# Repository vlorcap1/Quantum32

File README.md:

# Sistema de Análisis de Opiniones Distribuido I2C

## Changelog / Recent Updates (Quantum32 V3)
- **2025-12-22**:
  - **Fixed Blocking**: Master V3 now updates the OLED display continuously, even during high-speed Python batched sampling.
  - **Fixed Slave LED**: Slaves now explicitly use **Pin 7** for the status LED and give visual feedback on every I2C RX/TX event.
  - **Environment**: Fixed local Python environment initialization.

Sistema distribuido basado en Arduino que utiliza comunicación I2C para coordinar múltiples dispositivos esclavos que realizan análisis de opiniones (a favor/en contra/neutral). El maestro agrega los resultados y los muestra en una pantalla OLED con marcas de tiempo del RTC.

## 📋 Descripción

Este proyecto implementa una **simulación pedagógica de holografía (Toy Holography)** inspirada en el principio holográfico y la correspondencia AdS/CFT. Utiliza una arquitectura maestro-esclavo donde:

- **Maestro (Bulk)**: Representa el volumen ("bulk") del espacio-tiempo. Reconstruye información lógica a partir de las correlaciones de los esclavos, monitorea el ambiente y visualiza la "reconstrucción holográfica".
- **Esclavos (Boundary)**: Representan el borde ("boundary") del sistema. Generan observables locales con ruido y pérdida simulada que el maestro utiliza para inferir el estado del volumen.

El sistema ilustra cómo propiedades, corrección de errores y geometrías emergentes pueden surgir de interacciones distribuidas simples sobre un bus I2C.

## 🔧 Hardware Requerido

### Maestro (Master)
- 1x ESP32-S3 Super Mini (o compatible)
- 1x Pantalla OLED 1.3" (SH1106, dirección I2C 0x3C)
- 1x Módulo RTC DS3231 (dirección I2C 0x68)
- 1x Sensor BME280 (Temp/Hum/Pres, dirección I2C 0x76)
- 1x Módulo MicroSD (SPI: CS=7, MOSI=6, MISO=5, SCLK=4)
- 1x LED RGB (NeoPixel/WS2812B en pin 48)
- Resistencias pull-up 4.7kΩ (2x para SDA y SCL)

### Cada Esclavo (Slave)
- 1x Arduino (Uno, Nano, ESP32, etc.)
- Conexión al bus I2C compartido

### Adicional
- Cables jumper
- Fuente de alimentación adecuada (si se usan múltiples dispositivos)
- Protoboard o PCB para conexiones

### 2. Configurar el Maestro
1. Abrir `master.ino` en Arduino IDE
2. Revisar `config.h` para ajustar configuraciones si es necesario (pines, direcciones, habilitar/deshabilitar módulos)
3. Conectar el Arduino maestro
4. Seleccionar placa y puerto correcto
5. Cargar el código

### 3. Configurar los Esclavos
Para **cada esclavo**:
1. Abrir `slave.ino` en Arduino IDE
2. **IMPORTANTE**: Cambiar la dirección I2C única:
   ```cpp
   #define SLAVE_ADDRESS 0x10  // Cambiar a 0x11, 0x12, 0x13, etc.
   ```
3. Conectar el Arduino esclavo
4. Cargar el código
5. Repetir para cada esclavo adicional

### 4. Conexiones de Hardware
Ver [WIRING.md](WIRING.md) para diagramas detallados de conexión.

**Conexiones básicas I2C:**
- Conectar **SDA** de todos los dispositivos juntos
- Conectar **SCL** de todos los dispositivos juntos
- Conectar **GND** común
- Agregar resistencias pull-up de 4.7kΩ en SDA y SCL al voltaje de alimentación (3.3V o 5V según dispositivos)

## ⚙️ Configuración Avanzada

### Agregar Más Esclavos
1. Editar `config.h` en el maestro:
   ```cpp
   const uint8_t SLAVE_ADDRESSES[] = {
     SLAVE_ADDR_1,
     SLAVE_ADDR_2,
     SLAVE_ADDR_3,
     SLAVE_ADDR_4,
     0x14,  // Nuevo esclavo 5
     0x15   // Nuevo esclavo 6
   };
   ```
2. Programar nuevos esclavos con direcciones únicas
3. Conectar al bus I2C

### Habilitar/Deshabilitar Módulos
En `config.h` puedes activar o desactivar componentes:
```cpp
#define ENABLE_OLED       true   // Pantalla OLED
#define ENABLE_RTC        true   // Reloj RTC
#define ENABLE_SD_LOGGING true   // Registro en SD
#define ENABLE_BME280     true   // Sensor ambiental
#define ENABLE_RGB_LED    true   // LED de estado
```

### Ajustar Velocidad I2C
En `config.h`:
```cpp
#define I2C_CLOCK_SPEED 100000  // 100 kHz (estándar) o 400000 (rápido)
```

## 📊 Uso

### Monitor Serial
Abrir el monitor serial (115200 baud) para ver:
- Escaneo de dispositivos I2C al inicio
- Resultados agregados en tiempo real
- Confirmación de escritura en SD (`>> Data saved to SD`)
- Mensajes de error o advertencias

### Pantalla OLED (MasterV2)
La pantalla ahora visualiza la dinámica de la simulación en tiempo real:
- **Header**: `T:####` (Contador de Ticks de simulación).
- **Status Row**: Estado de cada esclavo (Cuadro lleno = OK, Vacío = Missing).
- **Bulk Reconstruction**: Barra de progreso que muestra qué porcentaje de la lógica del "bulk" ha sido recuperada exitosamente desde el borde.
  - El porcentaje se muestra centrado con contraste dinámico para evitar solapamiento.
- **Boundary Map (2x2)**: Visualización matricial del ruido en cada esclavo (cuadros más llenos = menos ruido/mejor señal).
- **History Graph**: Un gráfico histórico a la derecha que muestra la evolución de la `Reconstruction Ratio` en los últimos 40 ticks.
- **Footer**: Máscaras de bits (Boundary/Bulk) y datos ambientales.

### Registro en Tarjeta SD
El sistema registra en `datalog.csv`:
`timestamp, tick, active_slaves, boundary_mask, bulk_mask, recon_ratio, loss_sum, noise_avg, temp, hum`

### Disclaimer de "Veracidad Científica"
> [!IMPORTANT]
> **Nota sobre la precisión científica**:
> Este código es un **"modelo de juguete" (toy model)** con fines educativos y de prototipado.
> *   **No es** una simulación cuántica real (no hay entrelazamiento cuántico real ni hamiltonianos complejos).
> *   La "Reconstrucción del Bulk" usa una lógica de máscaras de bits simplificada para *ilustrar* conceptos de corrección de errores cuánticos, pero no implementa un código corrección de errores (QECC) riguroso como el código de HaPPY o Shor.
> *   Su objetivo es proveer una intuición física de cómo información local en el borde puede redundar en información robusta en el volumen, usando hardware clásico accesible.

## 🔍 Solución de Problemas

### No se detectan dispositivos I2C
- Verificar conexiones SDA/SCL
- Confirmar resistencias pull-up instaladas (4.7kΩ)
- Revisar alimentación de todos los dispositivos
- Usar sketch de escaneo I2C para detectar dispositivos

### OLED no muestra nada
- Verificar dirección I2C (0x3C o 0x3D)
- Confirmar librería correcta (SH1106 vs SSD1306)
- Revisar conexiones y alimentación

### Esclavos no responden
- Verificar direcciones únicas para cada esclavo
- Confirmar que los esclavos están alimentados
- Revisar que el código del esclavo se cargó correctamente
- Verificar timeout en `config.h` (aumentar si es necesario)

### Error en SD Card
- Verificar conexiones SPI (CS, MOSI, MISO, SCLK)
- Asegurar que la tarjeta está formateada en FAT32
- Revisar si el archivo `datalog.csv` está abierto en otro lugar

## 🛠️ Desarrollo Futuro

Posibles mejoras:
- [ ] Implementar checksums para validación de datos
- [ ] Agregar comandos de configuración desde el maestro
- [ ] Interfaz web para visualización remota
- [ ] Modo de bajo consumo para operación con batería
- [*] Implementar cuantum life! revisa la carpeta cuantum_life para ver el código del juego de la vida. 

## 📊 Wikipedia Data Processor

**NUEVO**: Módulo de Python para procesar artículos de Wikipedia y convertirlos en representaciones numéricas para simulaciones cuánticas.

### Características
- Extracción automática de artículos desde Wikipedia
- Limpieza y procesamiento de texto
- Vectorización TF-IDF (conversión texto → números)
- Export en múltiples formatos (CSV, NPY, JSON)

### Inicio Rápido

```bash
# Instalar dependencias
pip install -r requirements.txt

# Ejecutar ejemplos
python ejemplo_uso.py

# O usar en tu código
from wikipedia_processor import WikipediaProcessor
processor = WikipediaProcessor(language='es')
data = processor.process_articles(['Mecánica cuántica', 'Qubit'])
processor.export_data(data)
```

### Documentación
- [Guía Rápida](QUICKSTART.md) - Inicio en 5 minutos
- [Documentación Completa](WIKIPEDIA_PROCESSOR_README.md) - Ejemplos y casos de uso
- [Script de Ejemplos](ejemplo_uso.py) - Demostraciones prácticas

**Beneficio**: Transforma artículos de Wikipedia en vectores numéricos listos para usar en simulaciones Quantum32.

## 👤 Autor

**Alejandro Rebolledo**  
Email: arebolledo@udd.cl  
Fecha: 2025-12-01  

**Atribución Original**
El código original fue creado por **Vicente Lorca** [@vlorcap](https://github.com/vlorcap) ; este proyecto es un derivado y el concepto inicial proviene de Vicente.

## 📄 Licencia

Este proyecto está licenciado bajo **Creative Commons Attribution-NonCommercial 4.0 International (CC BY-NC 4.0)**.

Ver el archivo [LICENSE](LICENSE) para más detalles.

### Descargo de Responsabilidad

Este código se proporciona "tal cual", sin garantías de ningún tipo, expresas o implícitas. El autor no se hace responsable de ningún daño o pérdida que pueda resultar del uso de este código. Úselo bajo su propio riesgo.

## 🤝 Contribuciones

Las contribuciones son bienvenidas. Por favor:
1. Fork el proyecto
2. Crea una rama para tu feature (`git checkout -b feature/AmazingFeature`)
3. Commit tus cambios (`git commit -m 'Add some AmazingFeature'`)
4. Push a la rama (`git push origin feature/AmazingFeature`)
5. Abre un Pull Request

## 📞 Soporte

Para preguntas o problemas, por favor abre un issue en el repositorio de GitHub.

---

**¡Gracias por usar este proyecto!** ⭐ Si te resulta útil, considera darle una estrella al repositorio.

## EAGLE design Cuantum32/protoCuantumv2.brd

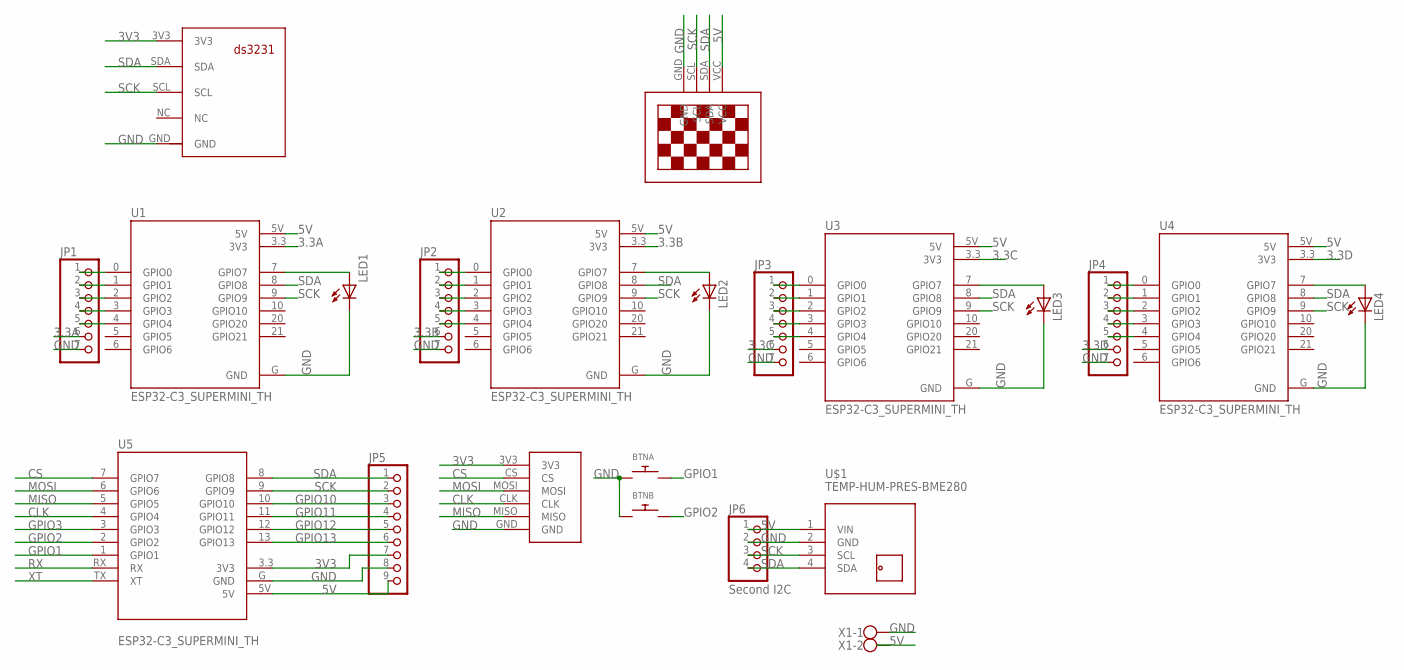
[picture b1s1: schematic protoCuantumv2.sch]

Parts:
BTNA: SWITCH_PUSHBUTTONEVQ-PE; TACT_PANA-EVQ
BTNB: SWITCH_PUSHBUTTONEVQ-PE; TACT_PANA-EVQ
JP1, JP2, JP3, JP4: PINHD-1X7; 1X07
JP5: PINHD-1X9; 1X09
JP6: Second I2C; 1X04
LED1, LED2, LED3, LED4: LED3MM
U1, U2, U3, U4, U5: ESP32-C3_SUPERMINI_TH; MODULE_ESP32-C3_SUPERMINI_TH
U$1: TEMP-HUM-PRES-BME280
U$2: SD_KUSKALLA
U$3: 13"OLED13"OLED; 1.3"OLED
U$4: RTC; RTCDS3231FP
X1: W237-102

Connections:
3.3A: JP1.6, U1.3.3 (3V3)
3.3B: JP2.6, U2.3.3 (3V3)
3.3C: JP3.6, U3.3.3 (3V3)
3.3D: JP4.6, U4.3.3 (3V3)
3V3: JP5.7, U5.3.3 (3V3), U$2.3V3, U$4.3V3
5V: JP5.9, JP6.1, U1.5V, U2.5V, U3.5V, U4.5V, U5.5V, U$1.1 (VIN), U$3.VCC, X1.2
CLK: U5.4 (GPIO4), U$2.CLK
CS: U5.7 (GPIO7), U$2.CS
GND: BTNA.P$1, BTNB.P$1, JP1.7, JP2.7, JP3.7, JP4.7, JP5.8, JP6.2, LED1.K (C), LED2.K (C), LED3.K (C), LED4.K (C), U1.G (GND), U2.G (GND), U3.G (GND), U4.G (GND), U5.G (GND), U$1.2 (GND), U$2.GND, U$3.GND, U$4.GND, X1.1
GPIO1: BTNA.P$2, U5.1 (GPIO1)
GPIO2: BTNB.P$2, U5.2 (GPIO2)
GPIO3: U5.3 (GPIO3)
GPIO10: JP5.3, U5.10 (GPIO10)
GPIO11: JP5.4, U5.11 (GPIO11)
GPIO12: JP5.5, U5.12 (GPIO12)
GPIO13: JP5.6, U5.13 (GPIO13)
MISO: U5.5 (GPIO5), U$2.MISO
MOSI: U5.6 (GPIO6), U$2.MOSI
unnamed: LED2.A, U2.7 (GPIO7)
unnamed: JP2.1, U2.0 (GPIO0)
unnamed: LED1.A, U1.7 (GPIO7)
unnamed: JP4.1, U4.0 (GPIO0)
unnamed: JP4.2, U4.1 (GPIO1)
unnamed: LED3.A, U3.7 (GPIO7)
unnamed: LED4.A, U4.7 (GPIO7)
unnamed: JP1.1, U1.0 (GPIO0)
unnamed: JP1.2, U1.1 (GPIO1)
unnamed: JP1.3, U1.2 (GPIO2)
unnamed: JP1.4, U1.3 (GPIO3)
unnamed: JP1.5, U1.4 (GPIO4)
unnamed: JP2.2, U2.1 (GPIO1)
unnamed: JP2.3, U2.2 (GPIO2)
unnamed: JP2.4, U2.3 (GPIO3)
unnamed: JP2.5, U2.4 (GPIO4)
unnamed: JP3.1, U3.0 (GPIO0)
unnamed: JP3.2, U3.1 (GPIO1)
unnamed: JP3.3, U3.2 (GPIO2)
unnamed: JP3.4, U3.3 (GPIO3)
unnamed: JP3.5, U3.4 (GPIO4)
unnamed: JP4.3, U4.2 (GPIO2)
unnamed: JP4.4, U4.3 (GPIO3)
unnamed: JP4.5, U4.4 (GPIO4)
RX: U5.RX
SCK: JP5.2, JP6.3, U1.9 (GPIO9), U2.9 (GPIO9), U3.9 (GPIO9), U4.9 (GPIO9), U5.9 (GPIO9), U$1.3 (SCL), U$3.SCL, U$4.SCL
SDA: JP5.1, JP6.4, U1.8 (GPIO8), U2.8 (GPIO8), U3.8 (GPIO8), U4.8 (GPIO8), U5.8 (GPIO8), U$1.4 (SDA), U$3.SDA, U$4.SDA
XT: U5.TX (XT)

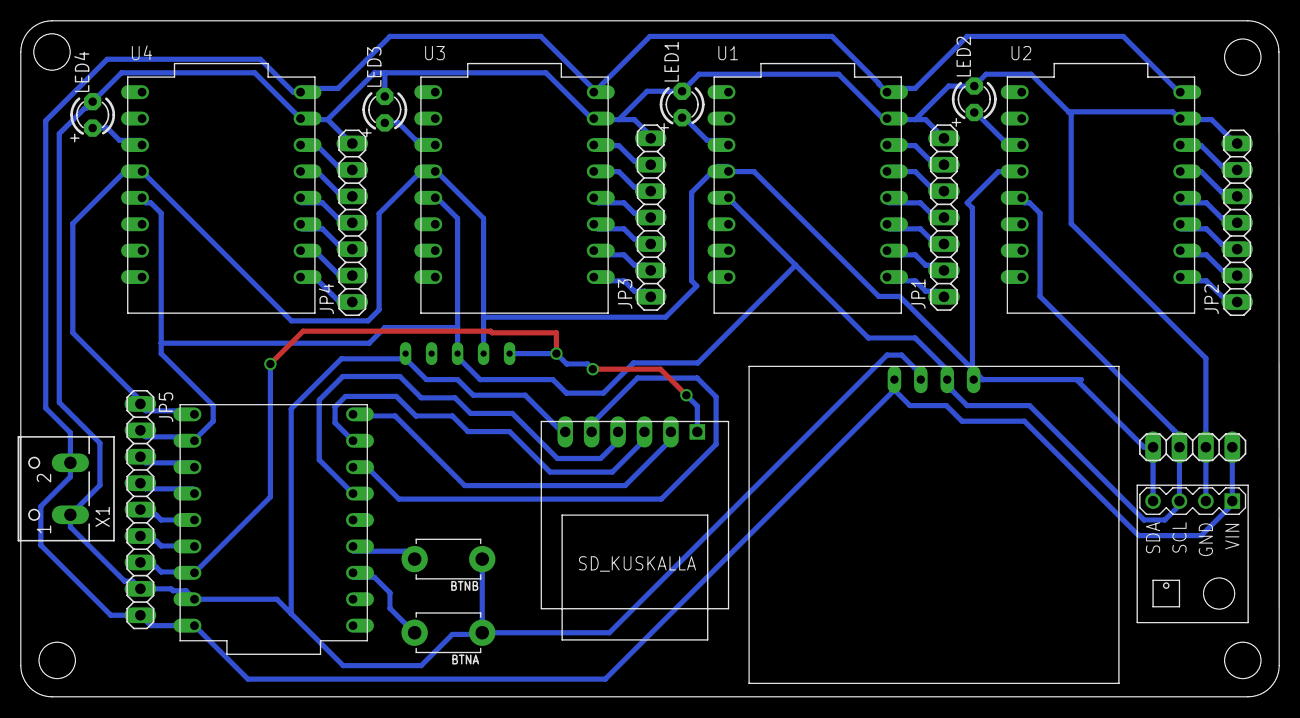
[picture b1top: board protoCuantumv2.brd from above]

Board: 2 copper layers, 121.0 x 65.0 mm, 22 parts (0 on the bottom side), 43 nets.

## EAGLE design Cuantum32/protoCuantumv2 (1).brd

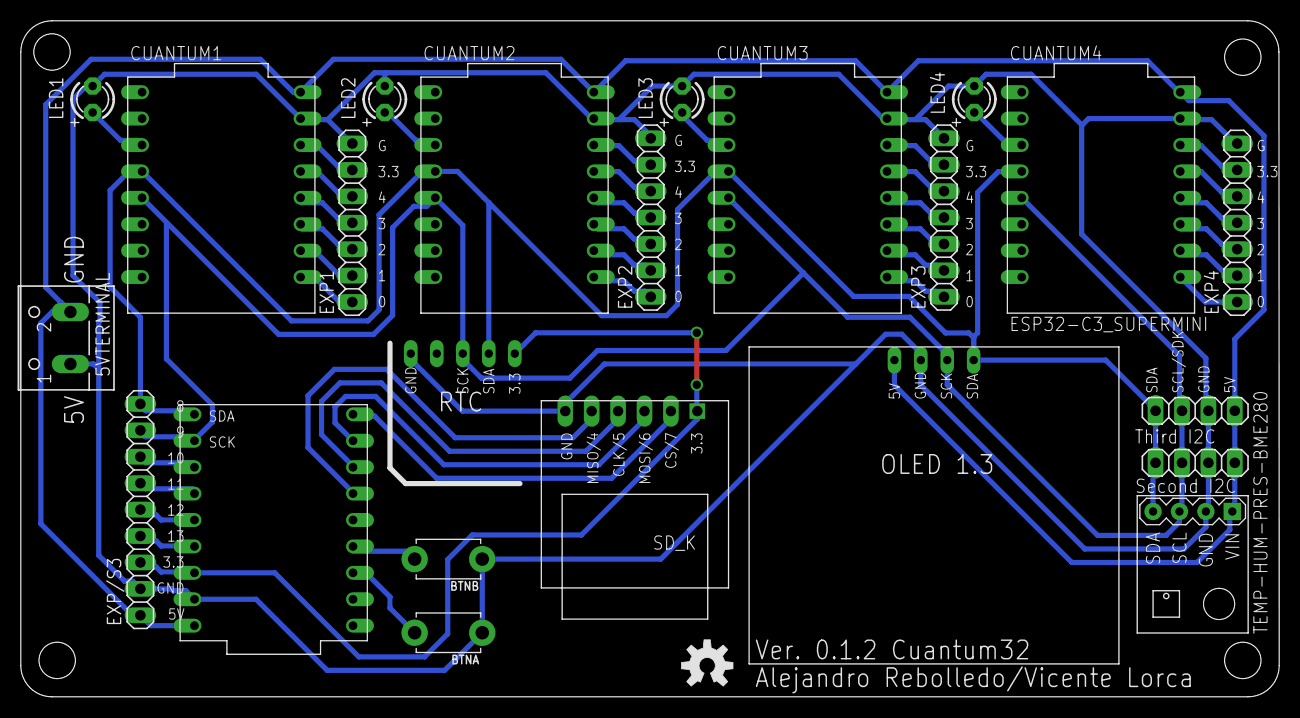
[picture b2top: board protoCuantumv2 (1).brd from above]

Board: 2 copper layers, 121.0 x 65.0 mm, 24 parts (0 on the bottom side), 43 nets.

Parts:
5VTERMINAL: W237-102
BTNA: TACT_PANA-EVQ
BTNB: TACT_PANA-EVQ
CUANTUM1, CUANTUM2, CUANTUM3, CUANTUM4: ESP32-C3_SUPERMINI; MODULE_ESP32-C3_SUPERMINI_TH
ESP32S3_SUPERMINI: ESP32-C3_SUPERMINI_TH; MODULE_ESP32-C3_SUPERMINI_TH
EXP1, EXP2, EXP3, EXP4: 1X07
EXP/S3: 1X09
JP1: Third I2C; 1X04
JP6: Second I2C; 1X04
LED1, LED2, LED3, LED4: LED3MM
LOGO1: OSHW-LOGOM; OSHW-LOGO-M
OLED1.3: 13"OLED13"OLED; 1.3"OLED
U$1: TEMP-HUM-PRES-BME280
U$2: SD_KUSKALLA
U$4: RTC; RTCDS3231FP

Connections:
3.3A: CUANTUM3.3.3, EXP3.6
3.3B: CUANTUM4.3.3, EXP4.6
3.3C: CUANTUM2.3.3, EXP2.6
3.3D: CUANTUM1.3.3, EXP1.6
3V3: ESP32S3_SUPERMINI.3.3, EXP/S3.7, U$2.3V3, U$4.3V3
5V: 5VTERMINAL.2, CUANTUM1.5V, CUANTUM2.5V, CUANTUM3.5V, CUANTUM4.5V, ESP32S3_SUPERMINI.5V, EXP/S3.9, JP1.1, JP6.1, OLED1.3.VCC, U$1.1
CLK: ESP32S3_SUPERMINI.5, U$2.CLK
CS: ESP32S3_SUPERMINI.7, U$2.CS
GND: 5VTERMINAL.1, BTNA.P$1, BTNB.P$1, CUANTUM1.G, CUANTUM2.G, CUANTUM3.G, CUANTUM4.G, ESP32S3_SUPERMINI.G, EXP1.7, EXP2.7, EXP3.7, EXP4.7, EXP/S3.8, JP1.2, JP6.2, LED1.K, LED2.K, LED3.K, LED4.K, OLED1.3.GND, U$1.2, U$2.GND, U$4.GND
GPIO1: BTNA.P$2, ESP32S3_SUPERMINI.1
GPIO2: BTNB.P$2, ESP32S3_SUPERMINI.2
GPIO10: ESP32S3_SUPERMINI.10, EXP/S3.3
GPIO11: ESP32S3_SUPERMINI.11, EXP/S3.4
GPIO12: ESP32S3_SUPERMINI.12, EXP/S3.5
GPIO13: ESP32S3_SUPERMINI.13, EXP/S3.6
MISO: ESP32S3_SUPERMINI.4, U$2.MISO
MOSI: ESP32S3_SUPERMINI.6, U$2.MOSI
unnamed: CUANTUM4.7, LED4.A
unnamed: CUANTUM4.0, EXP4.1
unnamed: CUANTUM3.7, LED3.A
unnamed: CUANTUM1.0, EXP1.1
unnamed: CUANTUM1.1, EXP1.2
unnamed: CUANTUM2.7, LED2.A
unnamed: CUANTUM1.7, LED1.A
unnamed: CUANTUM3.0, EXP3.1
unnamed: CUANTUM3.1, EXP3.2
unnamed: CUANTUM3.2, EXP3.3
unnamed: CUANTUM3.3, EXP3.4
unnamed: CUANTUM3.4, EXP3.5
unnamed: CUANTUM4.1, EXP4.2
unnamed: CUANTUM4.2, EXP4.3
unnamed: CUANTUM4.3, EXP4.4
unnamed: CUANTUM4.4, EXP4.5
unnamed: CUANTUM2.0, EXP2.1
unnamed: CUANTUM2.1, EXP2.2
unnamed: CUANTUM2.2, EXP2.3
unnamed: CUANTUM2.3, EXP2.4
unnamed: CUANTUM2.4, EXP2.5
unnamed: CUANTUM1.2, EXP1.3
unnamed: CUANTUM1.3, EXP1.4
unnamed: CUANTUM1.4, EXP1.5
SCK: CUANTUM1.9, CUANTUM2.9, CUANTUM3.9, CUANTUM4.9, ESP32S3_SUPERMINI.9, EXP/S3.2, JP1.3, JP6.3, OLED1.3.SCL, U$1.3, U$4.SCL
SDA: CUANTUM1.8, CUANTUM2.8, CUANTUM3.8, CUANTUM4.8, ESP32S3_SUPERMINI.8, EXP/S3.1, JP1.4, JP6.4, OLED1.3.SDA, U$1.4, U$4.SDA

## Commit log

2025-12-02 Add GitHub link for Vicente Lorca in attribution
2025-12-10 feat: Add initial protoCuantumv2 hardware design files and associated firmware project structure.
2025-12-11 Add files via upload
    la ultima version es la V3
2025-12-16 se sube paper de base
2025-12-16 feat: Introduce 'Toy Holography' simulation with new master/slave implementations, a dedicated visualization guide, and an updated project README.
2025-12-19 modelos 3d para enclusure
2025-12-22 feat: introduce non-blocking Toy Holography Master and Slave sketches with full peripheral support and robust serial/I2C communication.
2025-12-22 feat: Add initial PC client for Quantum32 Hybrid Sampler to solve Max-Cut problem, including documentation, graph visualization, and result logging.
2025-12-23 update explicacion
2025-12-29 feat: Initial implementation of the Quantum32 Hybrid Sampler web portal, including UI, logic, styling, and server instructions.
2026-01-02 Initial plan
2026-01-02 Add Wikipedia data processor for Quantum32 simulations
2026-01-02 Address code review feedback: improve error handling and regex patterns
2026-01-02 Add quickstart guide and update main README with Wikipedia processor section

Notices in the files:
parts and their libraries:
diy-modules: Released under the Creative Commons Attribution 4.0 International License: http://creativecommons.org/licenses/by/4.0
SparkFun-Aesthetics: Licensing: Creative Commons ShareAlike 4.0 International - https://creativecommons.org/licenses/by-sa/4.0
